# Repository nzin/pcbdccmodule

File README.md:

# pcbdccmodule
PCB schematic for a module train layout

BOM:
- mouser: 2x 651-1729209
- mouser: 2x 651-1729160
- mouser: 5x 523-RJHSE-7360
- mouser: 4x 806-KF85X-ED-9S-BR
- 3x bipolar red/green led: http://www.ledsales.com.au/index.php?main_page=product_info&products_id=1683
- resistors: 3x 2.5k

cable:
- mouser: 2x 523-L717-DE09P
- mouser: 2x 617-09-67-009-0424
- mouser: 538-19267-0123
- + 20 AWG black (mouser: 602-3053-100-02) /blue/yellow/orange

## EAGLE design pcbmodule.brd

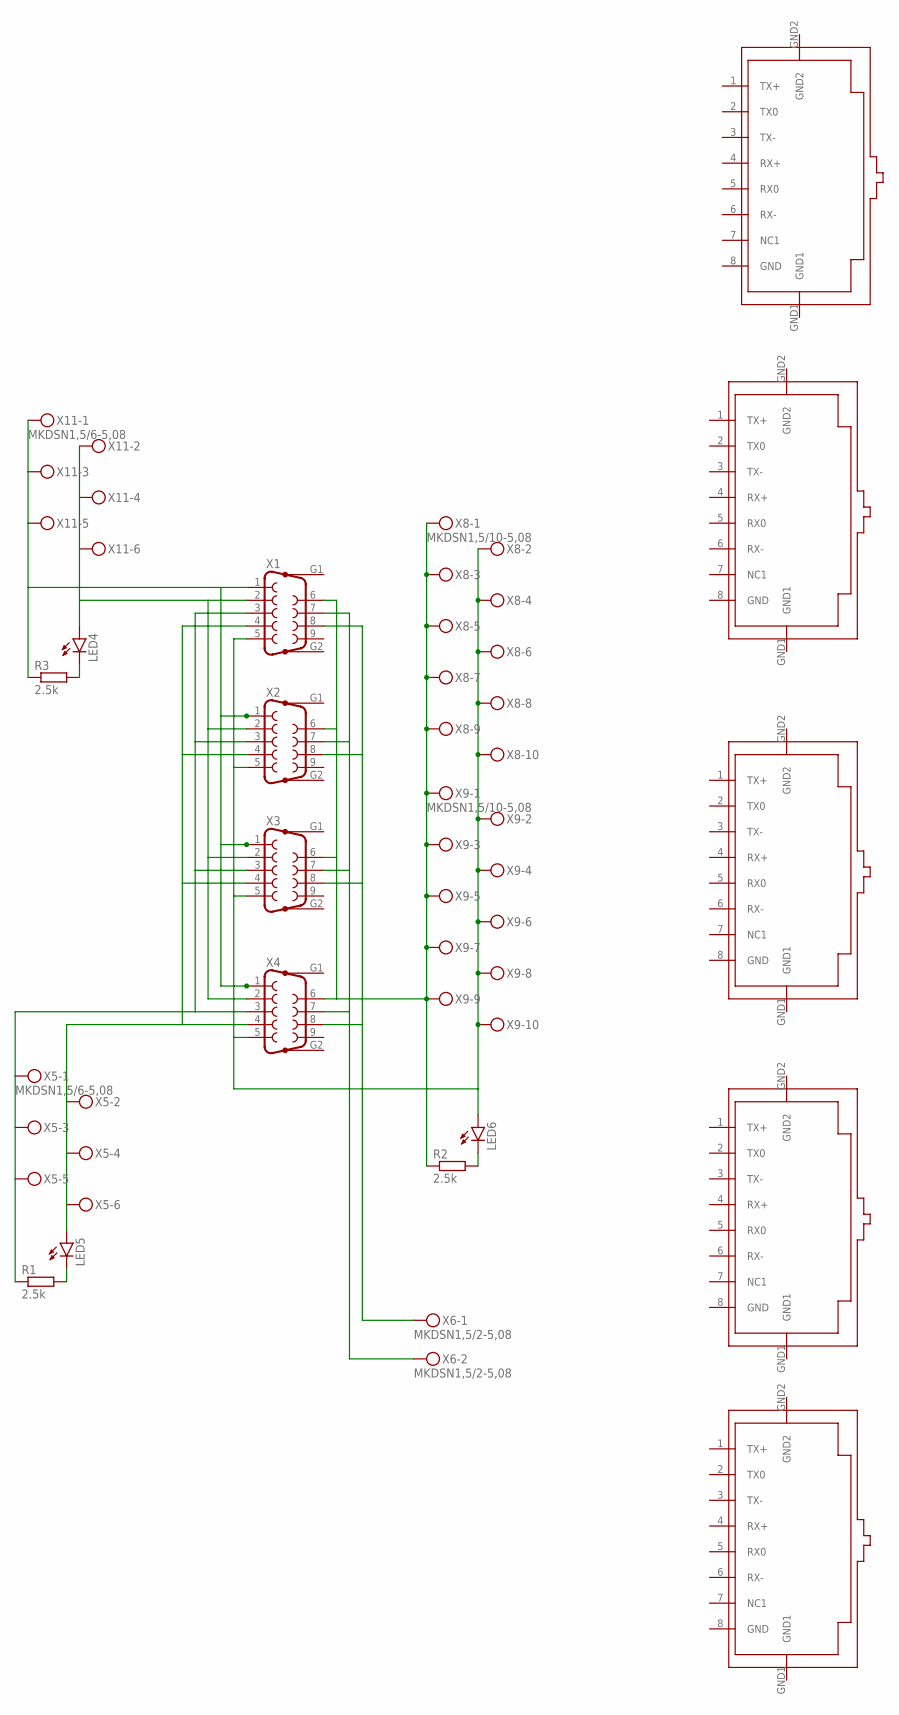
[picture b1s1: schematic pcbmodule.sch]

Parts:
LED4, LED5, LED6: LED5MM
R1, R2, R3: 2.5k; 0204/7
U$1, U$2, U$3, U$4, U$5: RJ45-TRAFO; RJ45-RJHSE5E8X
X1, X2, X3, X4: F09VP
X5, X11: MKDSN1,5/6-5,08
X6: MKDSN1,5/2-5,08
X8, X9: MKDSN1,5/10-5,08

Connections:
unnamed: R3.1, X1.1, X2.1, X3.1, X4.1, X11.1, X11.3, X11.5
unnamed: LED4.A, X1.2, X2.2, X3.2, X4.2, X11.2, X11.4, X11.6
unnamed: R1.1, X1.3, X2.3, X3.3, X4.3, X5.1, X5.3, X5.5
unnamed: LED4.K (C), R3.2
unnamed: LED5.A, X1.4, X2.4, X3.4, X4.4, X5.2, X5.4, X5.6
unnamed: LED6.A, X1.5, X2.5, X3.5, X4.5, X8.2, X8.4, X8.6, X8.8, X8.10, X9.2, X9.4, X9.6, X9.8, X9.10
unnamed: LED5.K (C), R1.2
unnamed: LED6.K (C), R2.2
unnamed: R2.1, X1.6, X2.6, X3.6, X4.6, X8.1, X8.3, X8.5, X8.7, X8.9, X9.1, X9.3, X9.5, X9.7, X9.9
unnamed: X1.7, X2.7, X3.7, X4.7, X6.2
unnamed: X1.8, X2.8, X3.8, X4.8, X6.1

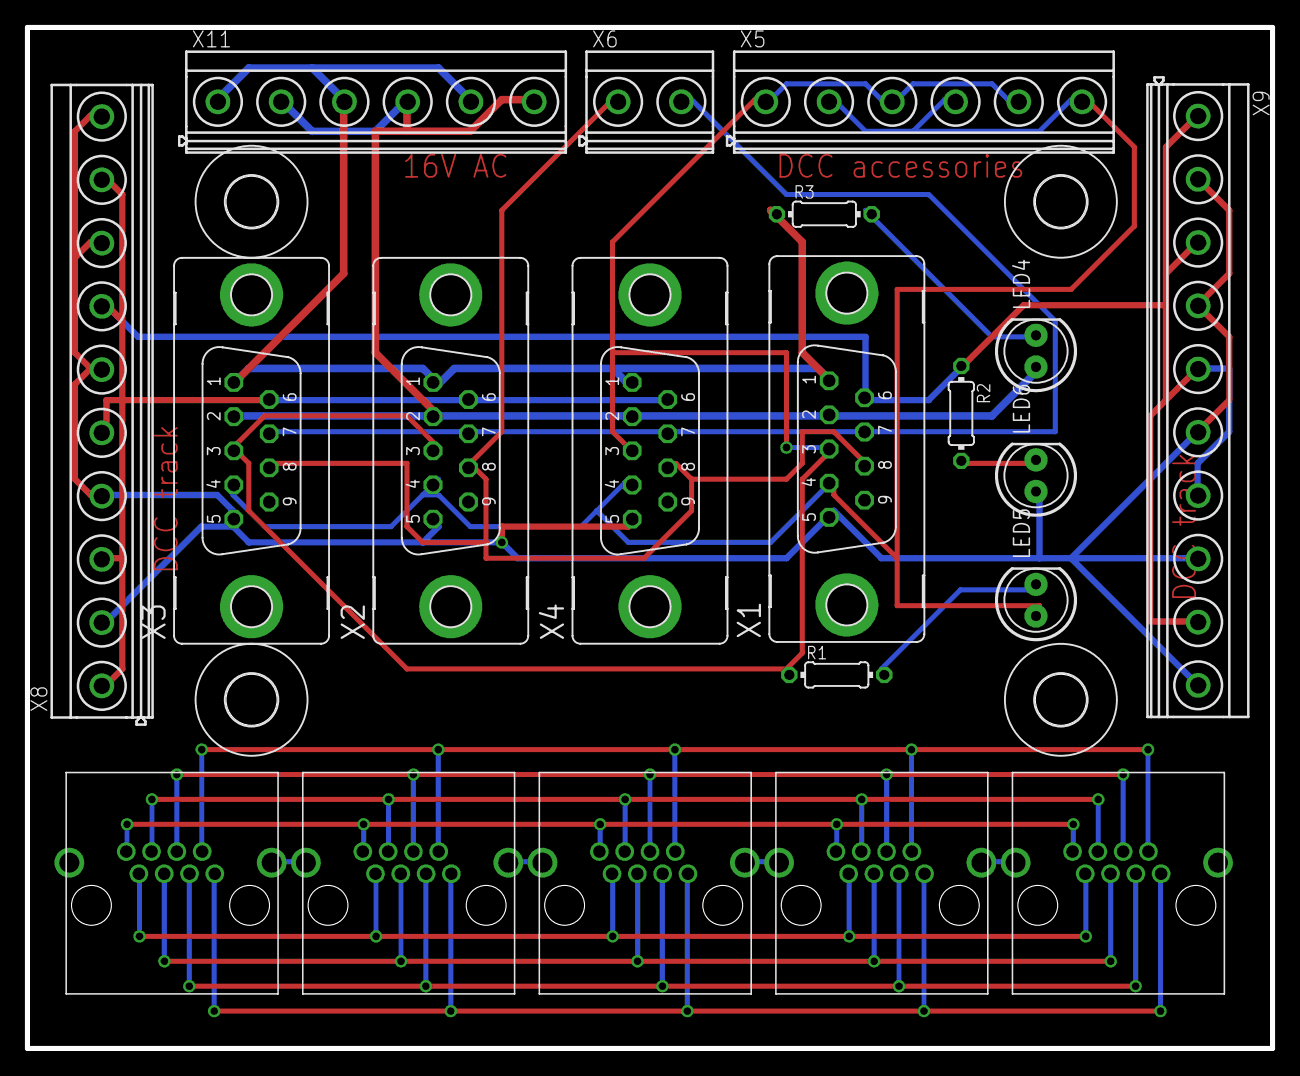
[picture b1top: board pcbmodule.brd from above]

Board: 2 copper layers, 100.0 x 82.0 mm, 24 parts (0 on the bottom side), 11 nets.

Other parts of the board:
U$6, U$7, U$8, U$9: 4,1

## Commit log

2016-02-14 first layout board, for: - 16AC signal, DCC accessories signal, DCC track signal, and not-used signal - Loconet signal
2016-02-14 Add BOM
2016-02-15 add led indicator (bipolar red/green led: http://www.ledsales.com.au/index.php?main_page=product_info&products_id=1683)
2016-02-16 update BOM
2016-02-19 update schema for proper RJ45 module layout
2016-02-20 reduce the size to 10 cm wide
2016-03-27 Make some space to be able to plugin connector in an easier way
2016-04-03 the Gerber file completed
2016-04-14 - change spec for rj12 (instead of rj45) - add a 4th circuit line for (analogic) metric n lines

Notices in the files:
parts and their libraries:
SparkFun-LED: Licensing: Creative Commons ShareAlike 4.0 International - https://creativecommons.org/licenses/by-sa/4.0
